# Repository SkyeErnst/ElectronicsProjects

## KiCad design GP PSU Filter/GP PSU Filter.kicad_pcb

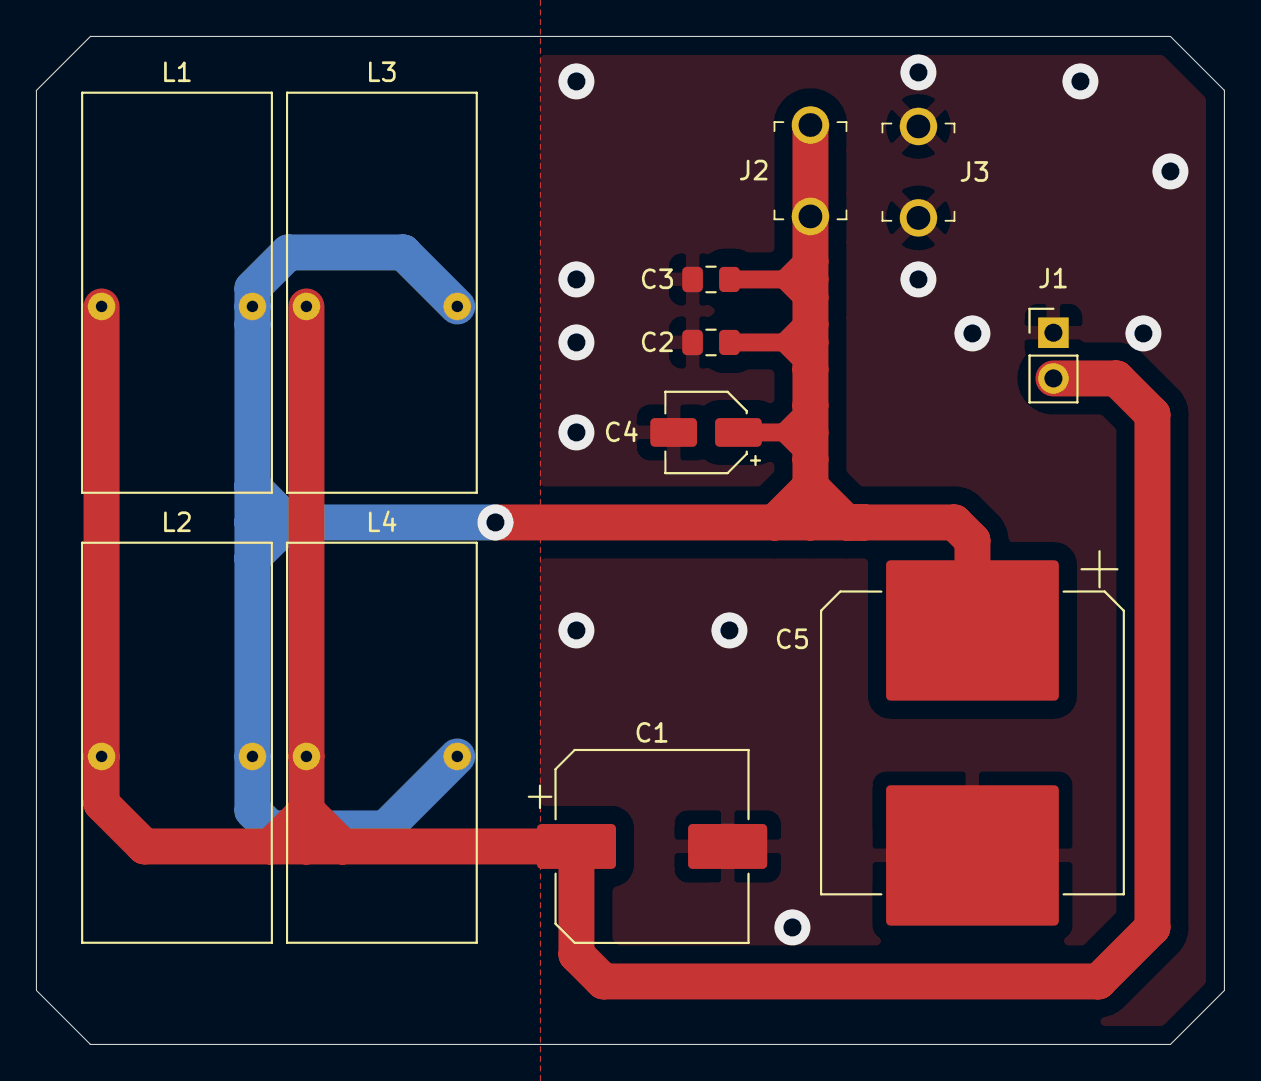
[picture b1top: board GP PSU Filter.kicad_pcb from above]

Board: 2 copper layers, 66.0 x 56.0 mm, 12 parts (0 on the bottom side), 3 nets.

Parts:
C1: 470uF; CP_Elec_10x14.3
C2: 10nF; C_0805_2012Metric_Pad1.15x1.40mm_HandSolder
C3: 100nF; C_0805_2012Metric_Pad1.15x1.40mm_HandSolder
C4: 10uF; CP_Elec_4x5.8
C5: 1mF; CP_Elec_16x17.5
J1: Conn_01x02; PinHeader_1x02_P2.54mm_Vertical
J2: 105-1102-001; Test_Jack_Horiz
J3: 105-1103-001; Test_Jack_Horiz
L1, L2, L3, L4: 100uH; Bourns-5729-RC

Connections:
GND: C1.2, C2.2, C3.2, C4.2, C5.2, J1.1, J3.1
unnamed: C2.1, C3.1, C4.1, C5.1, J2.1, L1.2, L2.2, L3.2, L4.2
VCC: C1.1, J1.2, L1.1, L2.1, L3.1, L4.1

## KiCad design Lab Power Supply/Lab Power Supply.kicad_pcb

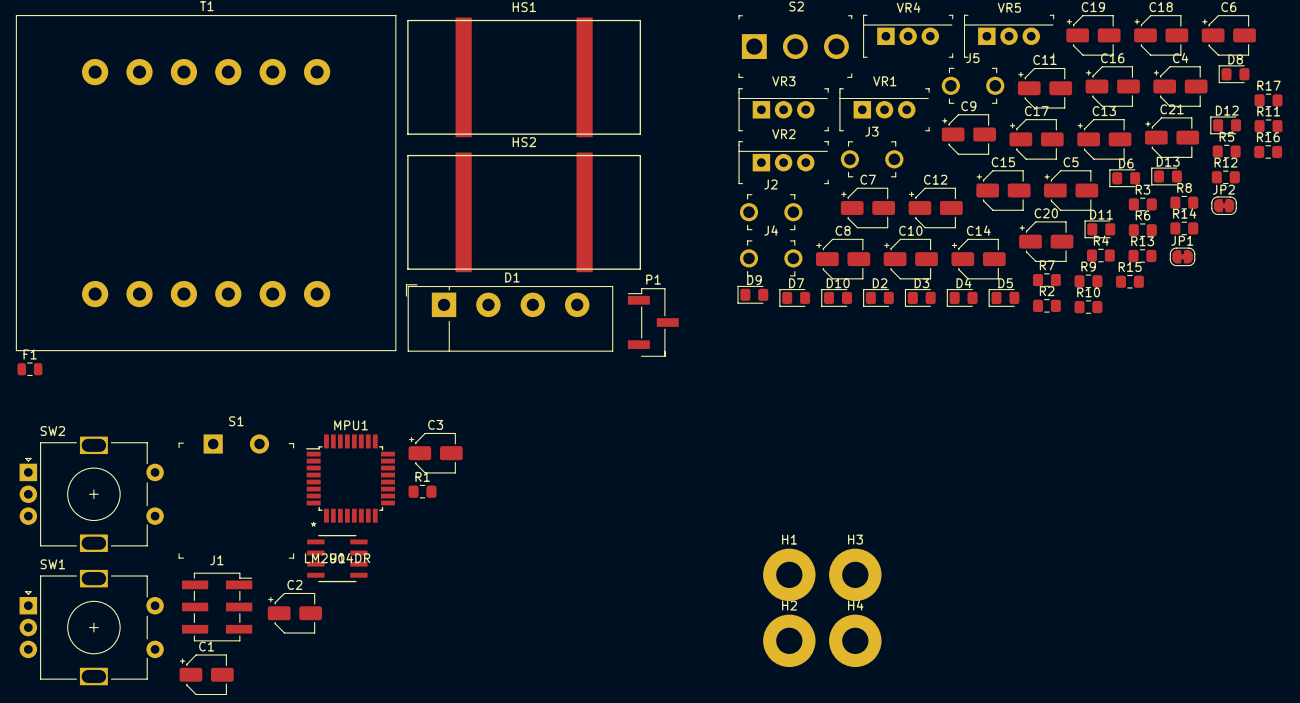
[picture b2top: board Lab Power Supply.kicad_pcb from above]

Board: 2 copper layers, 78 parts (0 on the bottom side), 40 nets, no tracks yet.

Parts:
C1, C4, C5, C11, C12, C15, C20, C21: 10uF; CP_Elec_4x5.8
C2, C3, C7, C8, C9, C10, C13, C14, C16, C17, C18, C19: 1uF; CP_Elec_4x5.8
C6: 0.22uF; CP_Elec_4x5.8
D1: Full Bridge; Diode_Bridge_Vishay_KBU
D2, D3, D5, D6, D8, D9, D10, D11, D12, D13: D; D_0805_2012Metric_Pad1.15x1.40mm_HandSolder
D4, D7: LED; LED_0805_2012Metric_Pad1.15x1.40mm_HandSolder
F1: Fuse; Fuse_0805_2012Metric
H1, H2, H3, H4: MountingHole_Pad; MountingHole_3mm_Pad
HS1, HS2: Heatsink_Pad; Heatsink_AAVID_573300D00010G_TO-263
J1: Programing Header; PinSocket_2x03_P2.54mm_Vertical_SMD
J2, J3: 105-1102-001; Test_Jack_Horiz
J4, J5: 105-1103-001; Test_Jack_Horiz
JP1, JP2: Jumper_NC_Small; SolderJumper-2_P1.3mm_Bridged_RoundedPad1.0x1.5mm
MPU1: ATxmega32E5-AU; TQFP-32_7x7mm_P0.8mm
P1: Conn_WallPlug_Earth; PinHeader_1x03_P2.54mm_Vertical_SMD_Pin1Left
R1: 2k; R_0805_2012Metric_Pad1.15x1.40mm_HandSolder
R2, R4: 680; R_0805_2012Metric_Pad1.15x1.40mm_HandSolder
R3: 100K; R_0805_2012Metric_Pad1.15x1.40mm_HandSolder
R5, R6, R12, R15, R16: 240; R_0805_2012Metric_Pad1.15x1.40mm_HandSolder
R7: 330; R_0805_2012Metric_Pad1.15x1.40mm_HandSolder
R8: 360; R_0805_2012Metric_Pad1.15x1.40mm_HandSolder
R9, R17: 370; R_0805_2012Metric_Pad1.15x1.40mm_HandSolder
R10, R11, R13, R14: 1Ω; R_0805_2012Metric_Pad1.15x1.40mm_HandSolder
S1: GPTS203211B; PushButton_12x12mm_THT_GPTS203211B
S2: 100SP1T1B4M2QE; Toggle_Switch_100SP1T1B4M2QE
SW1: RE Switch A; RotaryEncoder_Alps_EC11E-Switch_Vertical_H20mm
SW2: RE Switch B; RotaryEncoder_Alps_EC11E-Switch_Vertical_H20mm
T1: Transformer_1P_1S; Transformer_37x44
U1: LM2904DR
VR1, VR2, VR3, VR4, VR5: LM317T; TO-220-3

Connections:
+3V3: C10.1, D3.2, D6.1, MPU1.17, R6.1, VR2.2
+5V: C3.1, C8.1, C9.1, C13.1, D2.2, D3.1, D5.1, D8.1, R5.1, U1.8, VR1.2, VR2.3, VR3.3
/Digital Control and Display/3.3v_D: C1.1, C2.1, C14.1, D8.2, D11.1, MPU1.32, R1.1, R12.1, VR3.2
/Digital Control and Display/Vo1_MES: R11.2, R14.1, U1.3
/Digital Control and Display/Vo1_POP: MPU1.30, U1.1, U1.2
/Digital Control and Display/Vo2_MES: R10.2, R13.1, U1.5
/Digital Control and Display/Vo2_POP: MPU1.29, U1.6, U1.7
/PowerRegulation/PWR_AFT_SW: C4.1, C5.1, C6.1, C7.1, C16.1, C18.1, D2.1, D9.1, D10.1, R4.2, S2.2, VR1.3, VR4.3, VR5.3
/PowerRegulation/RAIL+: R2.2, S2.3
/PowerRegulation/Vo1: C17.1, D9.2, D12.1, JP1.2, R14.2, R15.1, VR4.2
/PowerRegulation/Vo2: C19.1, D10.2, D13.1, JP2.2, R13.2, R16.1, VR5.2
Earth: C1.2, C2.2, C3.2, C4.2, C5.2, C6.2, C7.2, C8.2, C9.2, C10.2, C11.2, C12.2, C13.2, C14.2, C15.2, C16.2, C17.2, C18.2, C19.2, C20.1, C20.2, C21.1, C21.2, D4.1, D7.1, D12.2, D13.2, H1.1, H2.1, H3.1, H4.1, J4.1, J5.1, MPU1.1, MPU1.3, MPU1.4, MPU1.6, MPU1.9, MPU1.10, MPU1.11, MPU1.12, MPU1.13, MPU1.14, MPU1.15, MPU1.16, MPU1.18, MPU1.21, P1.3, R3.1, R8.1, R9.1, R10.1, R11.1, R15.2, R16.2, R17.1, S1.1, U1.4, VR4.1, VR5.1
unnamed: C11.1, D5.2, R5.2, R7.2, VR1.1
unnamed: C12.1, D6.2, R6.2, R9.2, VR2.1
unnamed: C15.1, D11.2, R12.2, R17.2, VR3.1
unnamed: D1.3, T1.4
unnamed: D1.4, T1.3
unnamed: D4.2, R2.1
unnamed: D7.2, R4.1
unnamed: F1.1, T1.1
unnamed: F1.2, P1.1
unnamed: J1.1, MPU1.7
unnamed: J1.2, MPU1.20
unnamed: J1.3, MPU1.8, R1.2, S1.2
unnamed: J1.4, MPU1.19
unnamed: J2.1, JP1.1
unnamed: J3.1, JP2.1
unnamed: MPU1.2, SW1.C
unnamed: MPU1.5, SW1.A
unnamed: MPU1.22, SW2.A
unnamed: MPU1.23, SW2.C
unnamed: MPU1.24, SW2.B
unnamed: MPU1.25, SW2.S1
unnamed: MPU1.26, SW2.S2
unnamed: MPU1.27, SW1.S2
unnamed: MPU1.28, SW1.S1
unnamed: MPU1.31, SW1.B
unnamed: P1.2, T1.2
unnamed: R3.2, S2.1
unnamed: R7.1, R8.2

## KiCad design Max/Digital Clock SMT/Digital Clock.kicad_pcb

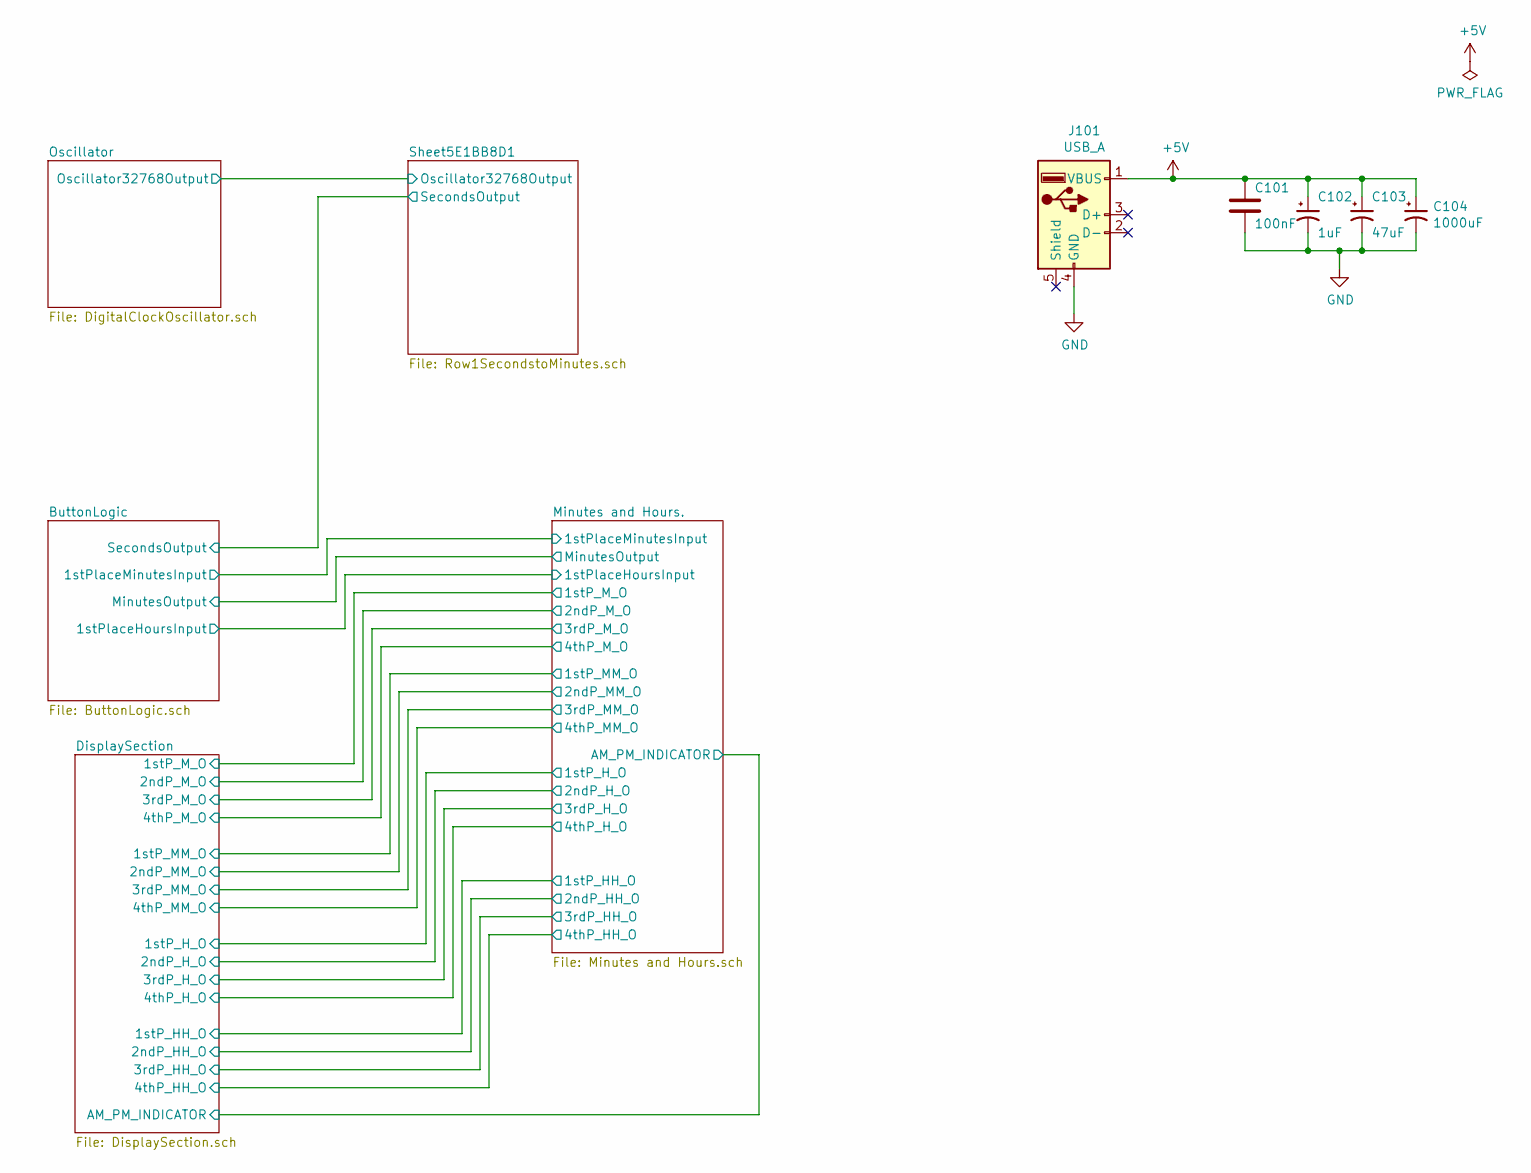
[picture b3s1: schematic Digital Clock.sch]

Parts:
C101: 100nF; C_0603_1608Metric_Pad1.05x0.95mm_HandSolder
C102: 1uF; CP_Elec_4x4.5
C103: 47uF; CP_Elec_5x5.4
C104: 1000uF; CP_Elec_10x10.5
J101: USB_A; USB_A_Female_UE27AC54100

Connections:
+5V: C101.1, C102.1, C103.1, C104.1, J101.1 (VBUS); also elsewhere on the board
GND: C101.2, C102.2, C103.2, C104.2, J101.4 (GND); also elsewhere on the board

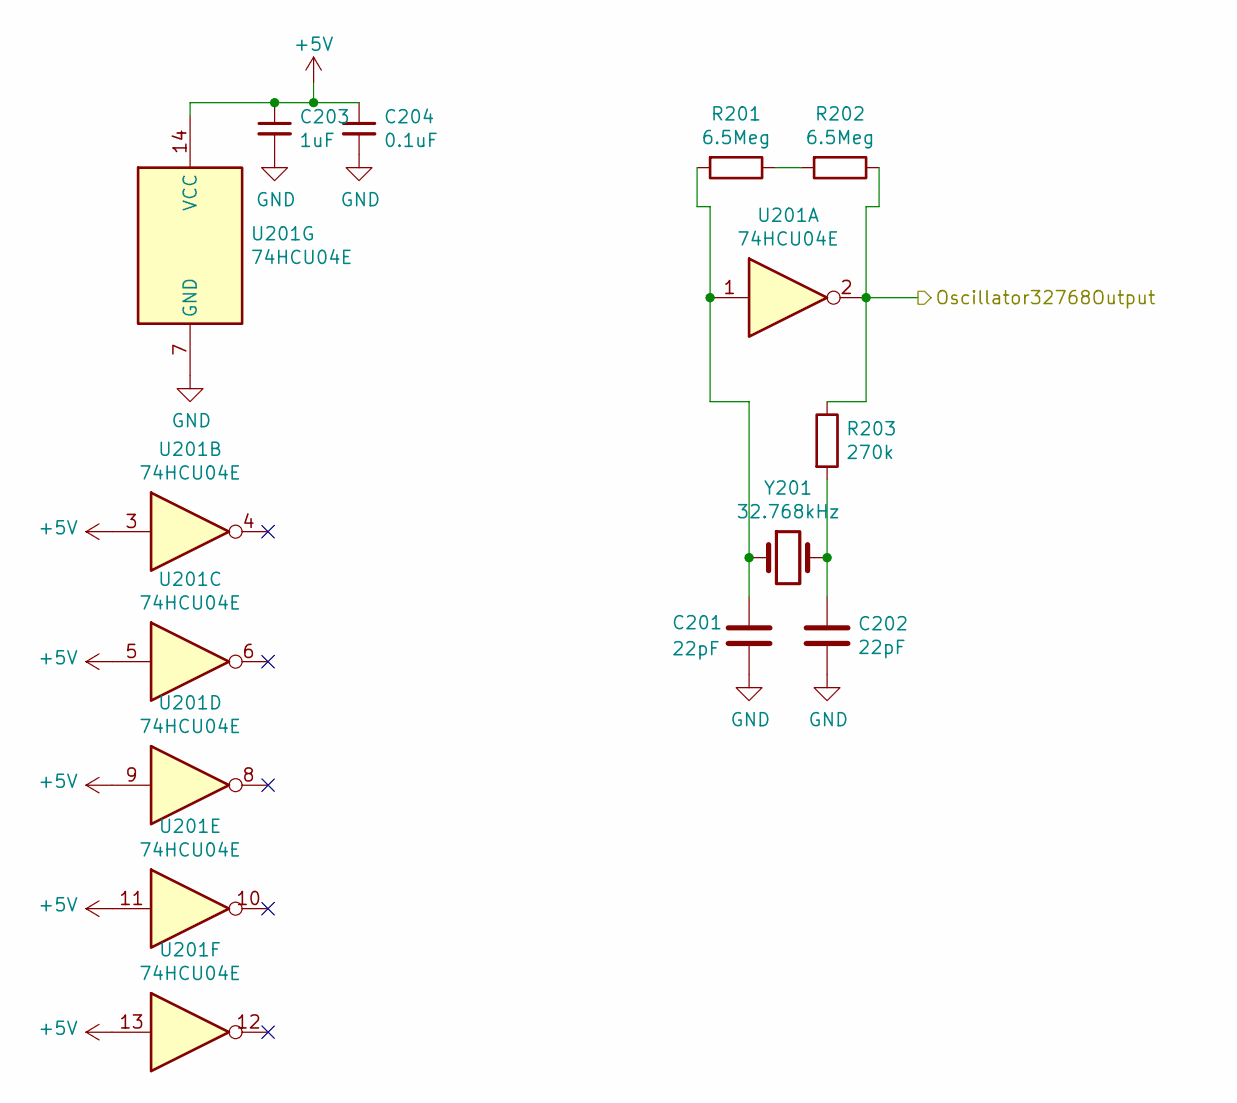
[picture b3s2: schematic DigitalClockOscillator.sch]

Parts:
C201, C202: 22pF; C_0805_2012Metric_Pad1.15x1.40mm_HandSolder
C203: 1uF; C_0805_2012Metric_Pad1.15x1.40mm_HandSolder
C204: 0.1uF; C_0805_2012Metric_Pad1.15x1.40mm_HandSolder
R201, R202: 6.5Meg; C_0805_2012Metric_Pad1.15x1.40mm_HandSolder
R203: 270k; C_0805_2012Metric_Pad1.15x1.40mm_HandSolder
U201: 74HCU04E; DIP-14_W7.62mm_LongPads
Y201: 32.768kHz; Crystal_Round_D2.0mm_Vertical

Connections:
+5V: C203.1, C204.1, U201.3, U201.5, U201.9, U201.11, U201.13, U201.14 (VCC); also elsewhere on the board
/Oscillator/Oscillator32768Output: R202.1, R203.1, U201.2; also elsewhere on the board
GND: C201.2, C202.2, C203.2, C204.2, U201.7 (GND); also elsewhere on the board
unnamed: C201.1, R201.2, U201.1, Y201.1
unnamed: C202.1, R203.2, Y201.2
unnamed: R201.1, R202.2

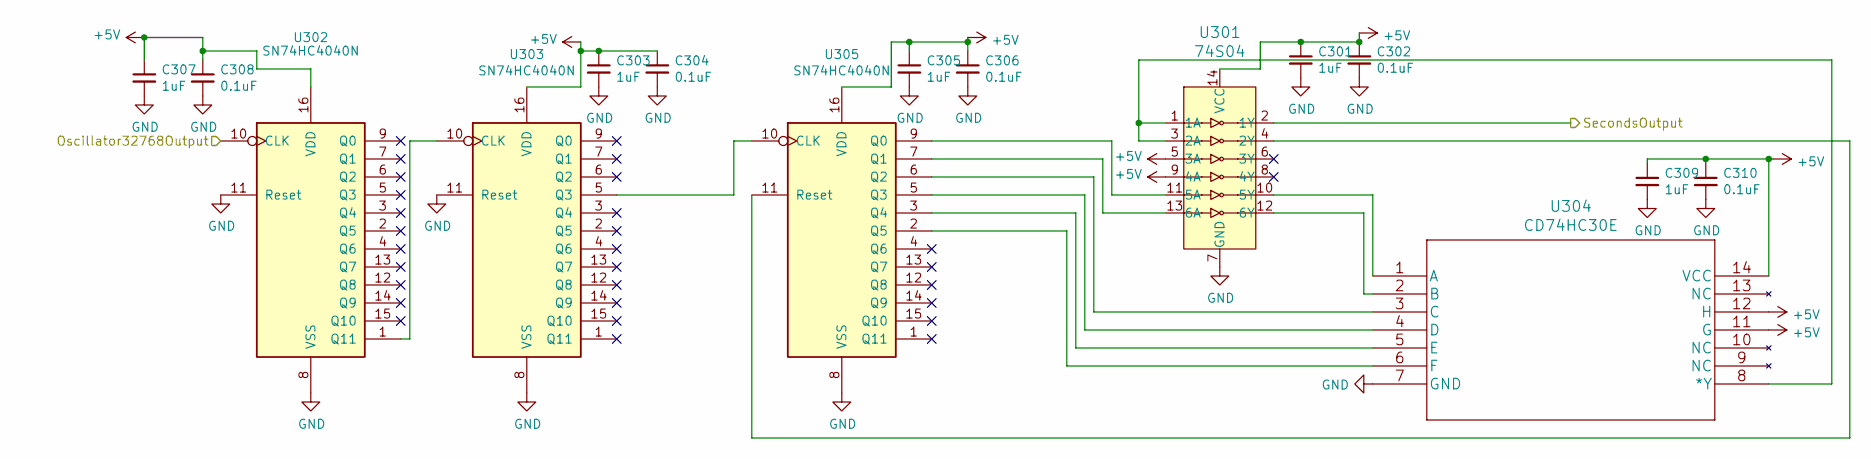
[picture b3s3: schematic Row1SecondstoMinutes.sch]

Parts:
C301, C303, C305, C307, C309: 1uF; C_0805_2012Metric_Pad1.15x1.40mm_HandSolder
C302, C304, C306, C308, C310: 0.1uF; C_0805_2012Metric_Pad1.15x1.40mm_HandSolder
U301: 74S04; SOIC-14_3.9x8.7mm_P1.27mm; MPN SN74LS04N; Digi-Key_PN 296-1629-5-ND
U302, U303, U305: SN74HC4040N; TSSOP-16_4.4x5mm_P0.65mm
U304: CD74HC30E; SOIC-14_3.9x8.7mm_P1.27mm

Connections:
+5V: C301.1, C302.1, C303.1, C304.1, C305.1, C306.1, C307.1, C308.1, C309.1, C310.1, U301.5 (3A), U301.9 (4A), U301.14 (VCC), U302.16 (VDD), U303.16 (VDD), U304.11 (G), U304.12 (H), U304.14 (VCC), U305.16 (VDD); also elsewhere on the board
/ButtonLogic/SecondsOutput: U301.2 (1Y); also elsewhere on the board
/Oscillator/Oscillator32768Output: U302.10 (CLK); also elsewhere on the board
GND: C301.2, C302.2, C303.2, C304.2, C305.2, C306.2, C307.2, C308.2, C309.2, C310.2, U301.7 (GND), U302.8 (VSS), U302.11 (Reset), U303.8 (VSS), U303.11 (Reset), U304.7 (GND), U305.8 (VSS); also elsewhere on the board
unnamed: U301.1 (1A), U301.3 (2A), U304.8 (*Y)
unnamed: U301.4 (2Y), U305.11 (Reset)
unnamed: U301.10 (5Y), U304.1 (A)
unnamed: U301.11 (5A), U305.9 (Q0)
unnamed: U301.12 (6Y), U304.2 (B)
unnamed: U301.13 (6A), U305.7 (Q1)
unnamed: U302.1 (Q11), U303.10 (CLK)
unnamed: U303.5 (Q3), U305.10 (CLK)
unnamed: U304.3 (C), U305.6 (Q2)
unnamed: U304.4 (D), U305.5 (Q3)
unnamed: U304.5 (E), U305.3 (Q4)
unnamed: U304.6 (F), U305.2 (Q5)

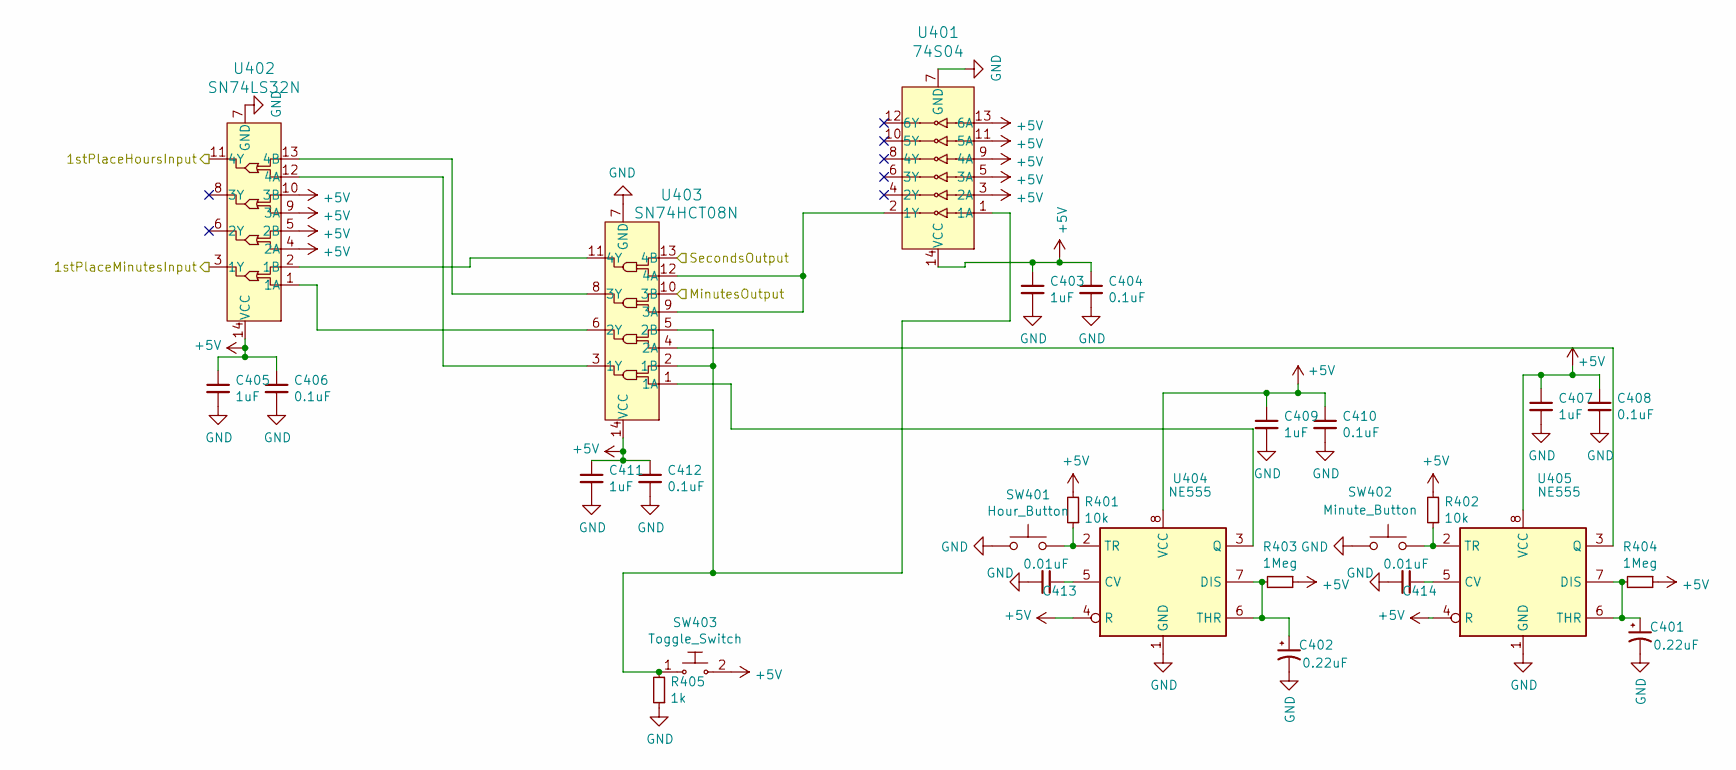
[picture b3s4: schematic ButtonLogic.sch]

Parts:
C401, C402: 0.22uF; CP_Elec_3x5.4
C403, C405, C407, C409, C411: 1uF; C_0805_2012Metric_Pad1.15x1.40mm_HandSolder
C404, C406, C408, C410, C412: 0.1uF; C_0805_2012Metric_Pad1.15x1.40mm_HandSolder
C413, C414: 0.01uF; C_0805_2012Metric_Pad1.15x1.40mm_HandSolder
R401, R402: 10k; C_0805_2012Metric_Pad1.15x1.40mm_HandSolder
R403, R404: 1Meg; C_0805_2012Metric_Pad1.15x1.40mm_HandSolder
R405: 1k; C_0805_2012Metric_Pad1.15x1.40mm_HandSolder
SW401: Hour_Button; PinHeader_2x01_P2.54mm_Vertical
SW402: Minute_Button; PinHeader_2x01_P2.54mm_Vertical
SW403: Toggle_Switch; PinHeader_2x01_P2.54mm_Vertical; MPN GPTS203211B; Digi-Key_PN CW181-ND
U401: 74S04; SOIC-14_3.9x8.7mm_P1.27mm; MPN SN74LS04N; Digi-Key_PN 296-1629-5-ND
U402: SN74LS32N; SSOP-14_5.3x6.2mm_P0.65mm; MPN SN74LS32N; Digi-Key_PN 296-1658-5-ND
U403: SN74HCT08N; TSSOP-14_4.4x5mm_P0.65mm; MPN SN74LS08N; Digi-Key_PN 296-1633-5-ND
U404, U405: NE555; SOIC-8_3.9x4.9mm_P1.27mm

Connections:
+5V: C403.1, C404.1, C405.1, C406.1, C407.1, C408.1, C409.1, C410.1, C411.1, C412.1, R401.2, R402.2, R403.1, R404.1, SW403.2, U401.3 (2A), U401.5 (3A), U401.9 (4A), U401.11 (5A), U401.13 (6A), U401.14 (VCC), U402.4 (2A), U402.5 (2B), U402.9 (3A), U402.10 (3B), U402.14 (VCC), U403.14 (VCC), U404.4 (R), U404.8 (VCC), U405.4 (R), U405.8 (VCC); also elsewhere on the board
/ButtonLogic/1stPlaceHoursInput: U402.11 (4Y); also elsewhere on the board
/ButtonLogic/1stPlaceMinutesInput: U402.3 (1Y); also elsewhere on the board
/ButtonLogic/MinutesOutput: U403.10 (3B); also elsewhere on the board
/ButtonLogic/SecondsOutput: U403.13 (4B); also elsewhere on the board
GND: C401.2, C402.2, C403.2, C404.2, C405.2, C406.2, C407.2, C408.2, C409.2, C410.2, C411.2, C412.2, C413.2, C414.2, R405.1, SW401.1, SW402.1, U401.7 (GND), U402.7 (GND), U403.7 (GND), U404.1 (GND), U405.1 (GND); also elsewhere on the board
unnamed: C401.1, R404.2, U405.6 (THR), U405.7 (DIS)
unnamed: C402.1, R403.2, U404.6 (THR), U404.7 (DIS)
unnamed: C413.1, U404.5 (CV)
unnamed: C414.1, U405.5 (CV)
unnamed: R401.1, SW401.2, U404.2 (TR)
unnamed: R402.1, SW402.2, U405.2 (TR)
unnamed: R405.2, SW403.1, U401.1 (1A), U403.2 (1B), U403.5 (2B)
unnamed: U401.2 (1Y), U403.9 (3A), U403.12 (4A)
unnamed: U402.1 (1A), U403.6 (2Y)
unnamed: U402.2 (1B), U403.11 (4Y)
unnamed: U402.12 (4A), U403.3 (1Y)
unnamed: U402.13 (4B), U403.8 (3Y)
unnamed: U403.1 (1A), U404.3 (Q)
unnamed: U403.4 (2A), U405.3 (Q)

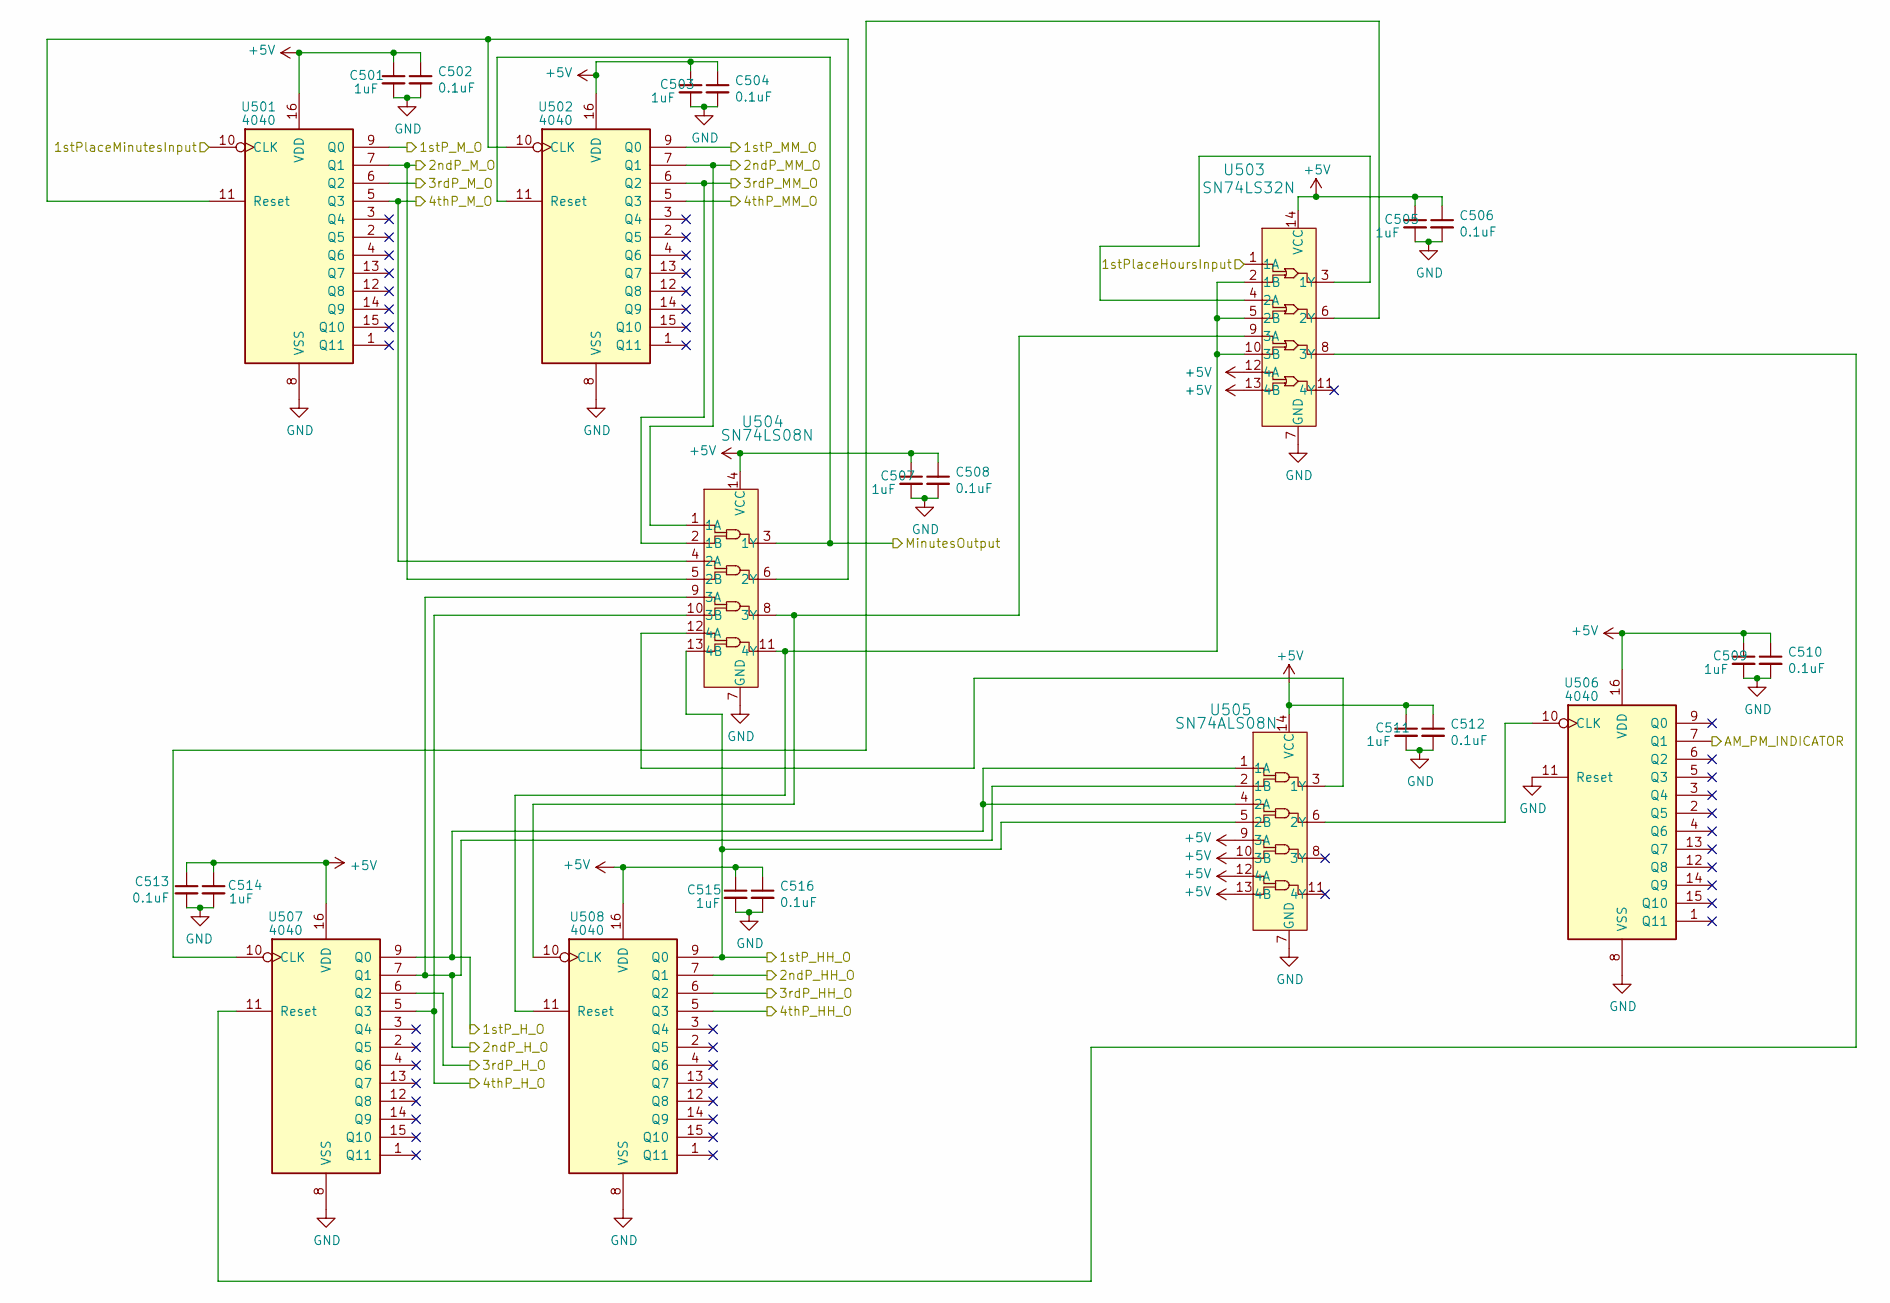
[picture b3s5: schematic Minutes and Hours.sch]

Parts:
C501, C503, C505, C507, C509, C511, C514, C515: 1uF; C_0805_2012Metric_Pad1.15x1.40mm_HandSolder
C502, C504, C506, C508, C510, C512, C513, C516: 0.1uF; C_0805_2012Metric_Pad1.15x1.40mm_HandSolder
U501, U502, U506, U507, U508: 4040; TSSOP-16_4.4x5mm_P0.65mm
U503: SN74LS32N; SSOP-14_5.3x6.2mm_P0.65mm; MPN SN74LS32N; Digi-Key_PN 296-1658-5-ND
U504: SN74LS08N; SOIC-14_3.9x8.7mm_P1.27mm; MPN SN74LS08N; Digi-Key_PN 296-1633-5-ND
U505: SN74ALS08N; SOIC-14_3.9x8.7mm_P1.27mm; MPN SN74LS08N; Digi-Key_PN 296-1633-5-ND

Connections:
+5V: C501.1, C502.1, C503.1, C504.1, C505.1, C506.1, C507.1, C508.1, C509.1, C510.1, C511.1, C512.1, C513.1, C514.1, C515.1, C516.1, U501.16 (VDD), U502.16 (VDD), U503.12 (4A), U503.13 (4B), U503.14 (VCC), U504.14 (VCC), U505.9 (3A), U505.10 (3B), U505.12 (4A), U505.13 (4B), U505.14 (VCC), U506.16 (VDD), U507.16 (VDD), U508.16 (VDD); also elsewhere on the board
/ButtonLogic/1stPlaceHoursInput: U503.1 (1A); also elsewhere on the board
/ButtonLogic/1stPlaceMinutesInput: U501.10 (CLK); also elsewhere on the board
/ButtonLogic/MinutesOutput: U502.11 (Reset), U504.3 (1Y); also elsewhere on the board
/DisplaySection/1stP_HH_O: U504.13 (4B), U505.5 (2B), U508.9 (Q0); also elsewhere on the board
/DisplaySection/1stP_H_O: U505.1 (1A), U505.4 (2A), U507.9 (Q0); also elsewhere on the board
/DisplaySection/1stP_MM_O: U502.9 (Q0); also elsewhere on the board
/DisplaySection/1stP_M_O: U501.9 (Q0); also elsewhere on the board
/DisplaySection/2ndP_HH_O: U508.7 (Q1); also elsewhere on the board
/DisplaySection/2ndP_H_O: U504.9 (3A), U505.2 (1B), U507.7 (Q1); also elsewhere on the board
/DisplaySection/2ndP_MM_O: U502.7 (Q1), U504.1 (1A); also elsewhere on the board
/DisplaySection/2ndP_M_O: U501.7 (Q1), U504.5 (2B); also elsewhere on the board
/DisplaySection/3rdP_HH_O: U508.6 (Q2); also elsewhere on the board
/DisplaySection/3rdP_H_O: U507.6 (Q2); also elsewhere on the board
/DisplaySection/3rdP_MM_O: U502.6 (Q2), U504.2 (1B); also elsewhere on the board
/DisplaySection/3rdP_M_O: U501.6 (Q2); also elsewhere on the board
/DisplaySection/4thP_HH_O: U508.5 (Q3); also elsewhere on the board
/DisplaySection/4thP_H_O: U504.10 (3B), U507.5 (Q3); also elsewhere on the board
/DisplaySection/4thP_MM_O: U502.5 (Q3); also elsewhere on the board
/DisplaySection/4thP_M_O: U501.5 (Q3), U504.4 (2A); also elsewhere on the board
/DisplaySection/AM_PM_INDICATOR: U506.7 (Q1); also elsewhere on the board
GND: C501.2, C502.2, C503.2, C504.2, C505.2, C506.2, C507.2, C508.2, C509.2, C510.2, C511.2, C512.2, C513.2, C514.2, C515.2, C516.2, U501.8 (VSS), U502.8 (VSS), U503.7 (GND), U504.7 (GND), U505.7 (GND), U506.8 (VSS), U506.11 (Reset), U507.8 (VSS), U508.8 (VSS); also elsewhere on the board
unnamed: U501.11 (Reset), U502.10 (CLK), U504.6 (2Y)
unnamed: U503.3 (1Y), U503.4 (2A)
unnamed: U503.6 (2Y), U507.10 (CLK)
unnamed: U503.8 (3Y), U507.11 (Reset)
unnamed: U503.9 (3A), U504.8 (3Y), U508.10 (CLK)
unnamed: U503.2 (1B), U503.5 (2B), U503.10 (3B), U504.11 (4Y), U508.11 (Reset)
unnamed: U504.12 (4A), U505.3 (1Y)
unnamed: U505.6 (2Y), U506.10 (CLK)

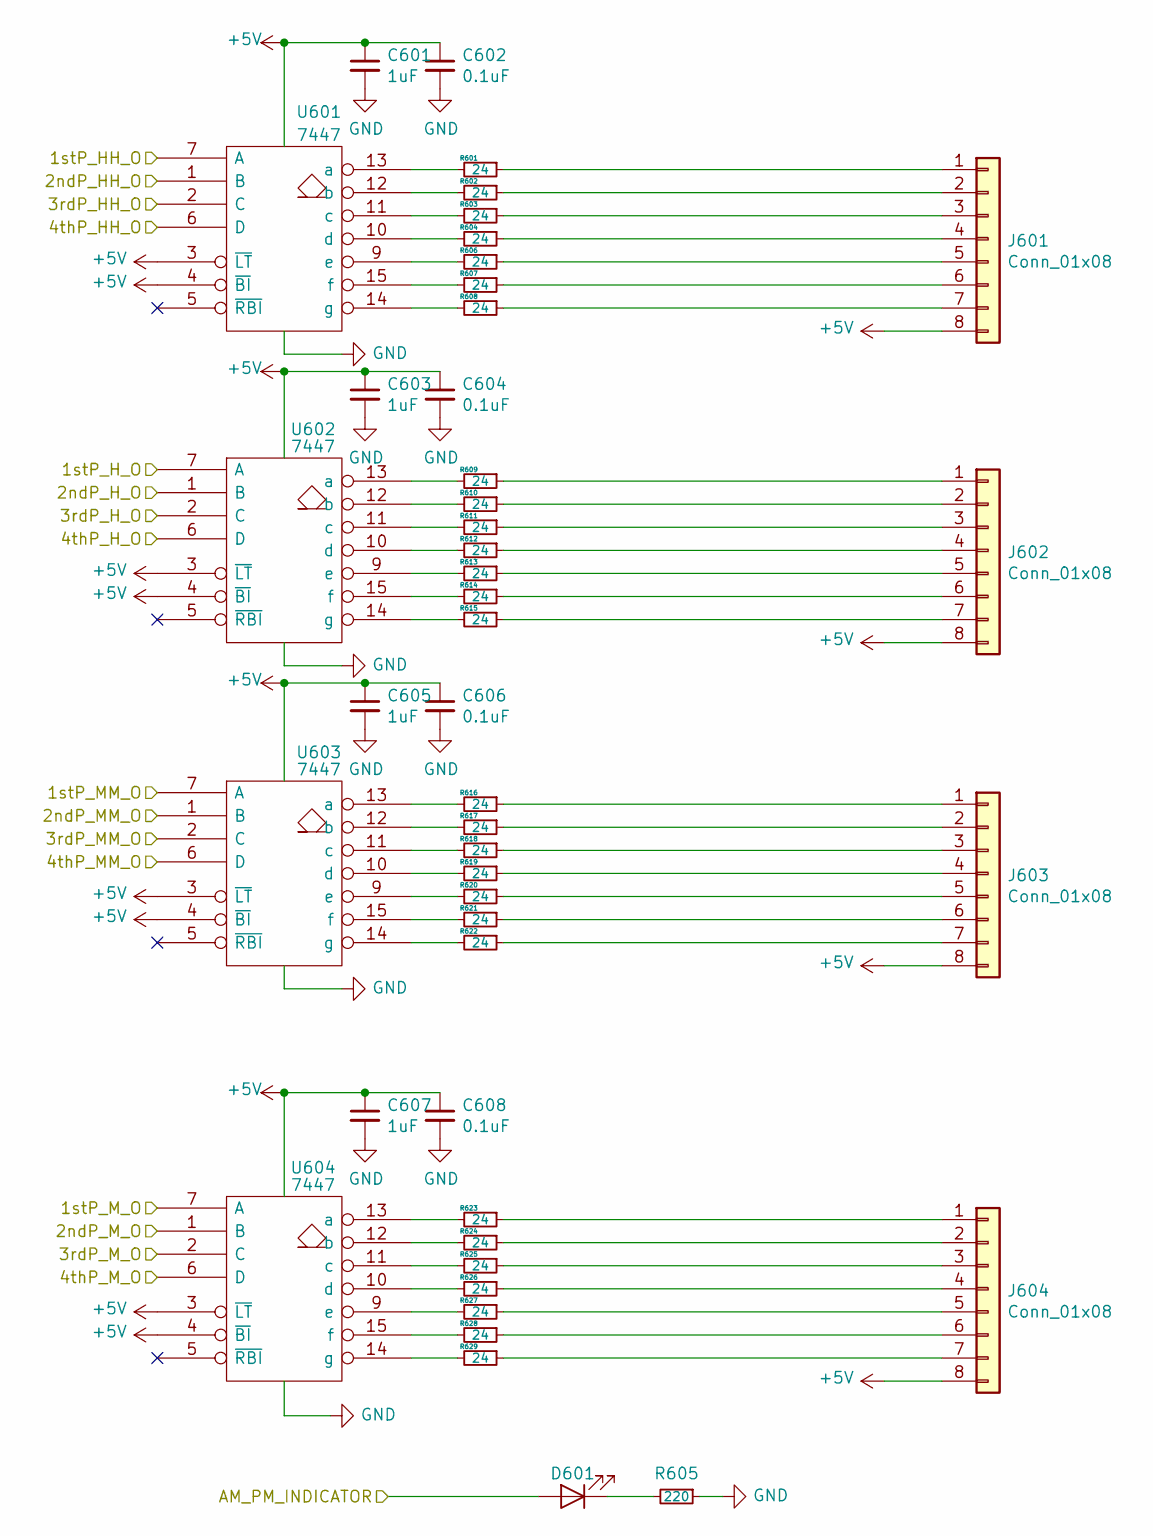
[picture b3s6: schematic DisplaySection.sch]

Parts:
C601, C603, C605, C607: 1uF; C_0805_2012Metric_Pad1.15x1.40mm_HandSolder
C602, C604, C606, C608: 0.1uF; C_0805_2012Metric_Pad1.15x1.40mm_HandSolder
D601: GREEN; LED_D3.0mm
J601, J602, J603, J604: Conn_01x08; PinHeader_1x08_P2.54mm_Vertical
R601, R602, R603, R604, R606, R607, R608, R609, R610, R611, R612, R613, R614, R615, R616, R617, R618, R619, R620, R621, R622, R623, R624, R625, R626, R627, R628, R629: 24; C_0805_2012Metric_Pad1.15x1.40mm_HandSolder
R605: 220; C_0805_2012Metric_Pad1.15x1.40mm_HandSolder
U601, U602, U603, U604: 7447; SOIC-16_3.9x9.9mm_P1.27mm

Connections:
+5V: C601.1, C602.1, C603.1, C604.1, C605.1, C606.1, C607.1, C608.1, J601.8, J602.8, J603.8, J604.8, U601.3 (~LT), U601.4 (~BI), U601.16 (VCC), U602.3 (~LT), U602.4 (~BI), U602.16 (VCC), U603.3 (~LT), U603.4 (~BI), U603.16 (VCC), U604.3 (~LT), U604.4 (~BI), U604.16 (VCC); also elsewhere on the board
/DisplaySection/1stP_HH_O: U601.7 (A); also elsewhere on the board
/DisplaySection/1stP_H_O: U602.7 (A); also elsewhere on the board
/DisplaySection/1stP_MM_O: U603.7 (A); also elsewhere on the board
/DisplaySection/1stP_M_O: U604.7 (A); also elsewhere on the board
/DisplaySection/2ndP_HH_O: U601.1 (B); also elsewhere on the board
/DisplaySection/2ndP_H_O: U602.1 (B); also elsewhere on the board
/DisplaySection/2ndP_MM_O: U603.1 (B); also elsewhere on the board
/DisplaySection/2ndP_M_O: U604.1 (B); also elsewhere on the board
/DisplaySection/3rdP_HH_O: U601.2 (C); also elsewhere on the board
/DisplaySection/3rdP_H_O: U602.2 (C); also elsewhere on the board
/DisplaySection/3rdP_MM_O: U603.2 (C); also elsewhere on the board
/DisplaySection/3rdP_M_O: U604.2 (C); also elsewhere on the board
/DisplaySection/4thP_HH_O: U601.6 (D); also elsewhere on the board
/DisplaySection/4thP_H_O: U602.6 (D); also elsewhere on the board
/DisplaySection/4thP_MM_O: U603.6 (D); also elsewhere on the board
/DisplaySection/4thP_M_O: U604.6 (D); also elsewhere on the board
/DisplaySection/AM_PM_INDICATOR: D601.2 (A); also elsewhere on the board
GND: C601.2, C602.2, C603.2, C604.2, C605.2, C606.2, C607.2, C608.2, R605.1, U601.8 (GND), U602.8 (GND), U603.8 (GND), U604.8 (GND); also elsewhere on the board
unnamed: D601.1 (K), R605.2
unnamed: J601.1, R601.1
unnamed: J601.2, R602.1
unnamed: J601.3, R603.1
unnamed: J601.4, R604.1
unnamed: J601.5, R606.1
unnamed: J601.6, R607.1
unnamed: J601.7, R608.1
unnamed: J602.1, R609.1
unnamed: J602.2, R610.1
unnamed: J602.3, R611.1
unnamed: J602.4, R612.1
unnamed: J602.5, R613.1
unnamed: J602.6, R614.1
unnamed: J602.7, R615.1
unnamed: J603.1, R616.1
unnamed: J603.2, R617.1
unnamed: J603.3, R618.1
unnamed: J603.4, R619.1
unnamed: J603.5, R620.1
unnamed: J603.6, R621.1
unnamed: J603.7, R622.1
unnamed: J604.1, R623.1
unnamed: J604.2, R624.1
unnamed: J604.3, R625.1
unnamed: J604.4, R626.1
unnamed: J604.5, R627.1
unnamed: J604.6, R628.1
unnamed: J604.7, R629.1
unnamed: R601.2, U601.13 (a)
unnamed: R602.2, U601.12 (b)
unnamed: R603.2, U601.11 (c)
unnamed: R604.2, U601.10 (d)
unnamed: R606.2, U601.9 (e)
unnamed: R607.2, U601.15 (f)
unnamed: R608.2, U601.14 (g)
unnamed: R609.2, U602.13 (a)
unnamed: R610.2, U602.12 (b)
unnamed: R611.2, U602.11 (c)
unnamed: R612.2, U602.10 (d)
unnamed: R613.2, U602.9 (e)
unnamed: R614.2, U602.15 (f)
unnamed: R615.2, U602.14 (g)
unnamed: R616.2, U603.13 (a)
unnamed: R617.2, U603.12 (b)
unnamed: R618.2, U603.11 (c)
unnamed: R619.2, U603.10 (d)
unnamed: R620.2, U603.9 (e)
unnamed: R621.2, U603.15 (f)
unnamed: R622.2, U603.14 (g)
unnamed: R623.2, U604.13 (a)
unnamed: R624.2, U604.12 (b)
unnamed: R625.2, U604.11 (c)
unnamed: R626.2, U604.10 (d)
unnamed: R627.2, U604.9 (e)
unnamed: R628.2, U604.15 (f)
unnamed: R629.2, U604.14 (g)

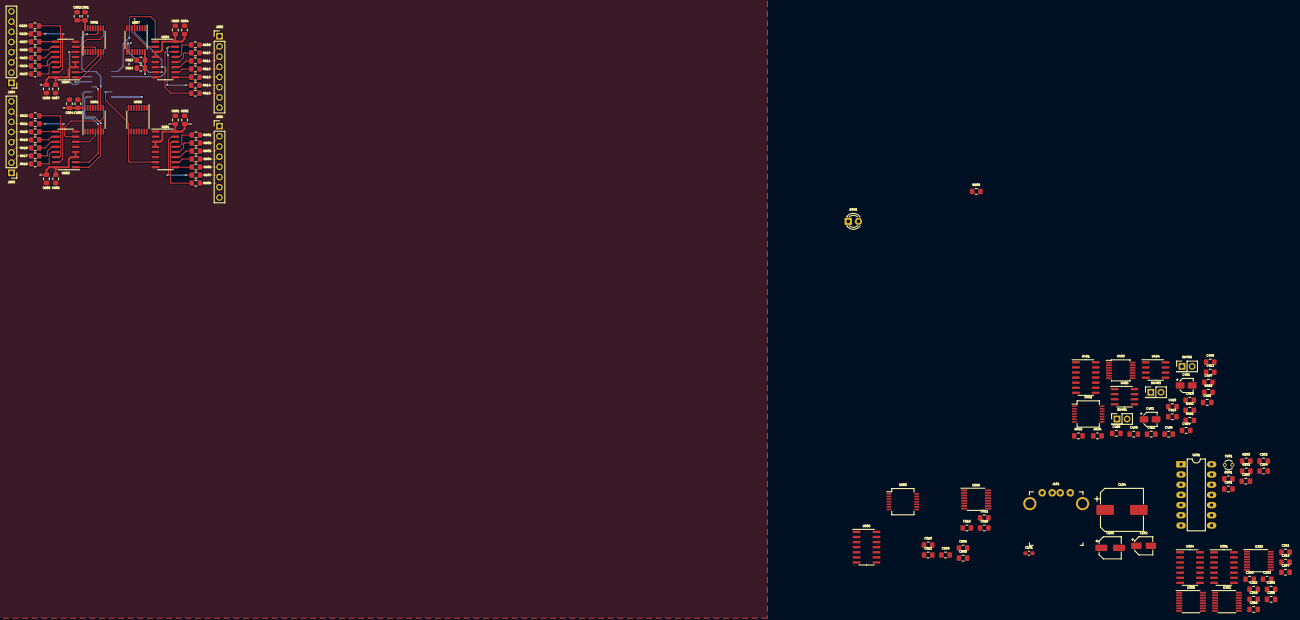
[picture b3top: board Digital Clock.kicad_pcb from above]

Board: 4 copper layers, 126 parts (0 on the bottom side), 118 nets.

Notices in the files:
parts and their libraries:
Copyright 2016 Accelerated Designs. All rights reserved.
